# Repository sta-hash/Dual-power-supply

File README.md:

# Dual-power-supply
this provide positive and negative supply in circuit.

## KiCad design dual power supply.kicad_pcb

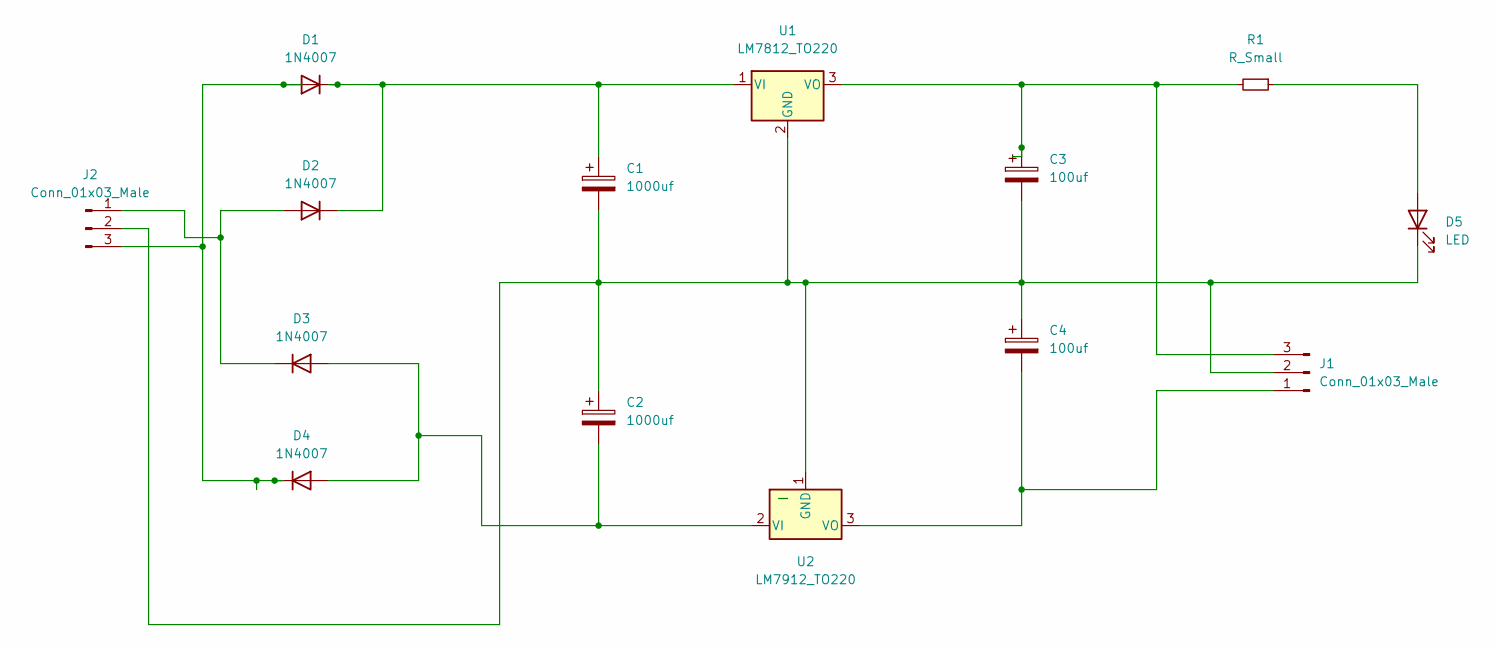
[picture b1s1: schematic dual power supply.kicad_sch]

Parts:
C1, C2: 1000uf; CP_Radial_D4.0mm_P2.00mm
C3, C4: 100uf; CP_Radial_D4.0mm_P2.00mm
D1, D2, D3, D4: 1N4007; D_DO-41_SOD81_P10.16mm_Horizontal
D5: LED; R_Axial_DIN0204_L3.6mm_D1.6mm_P1.90mm_Vertical
J1, J2: Conn_01x03_Male; SolderWire-0.1sqmm_1x03_P3.6mm_D0.4mm_OD1mm
R1: R_Small; R_Axial_DIN0204_L3.6mm_D1.6mm_P1.90mm_Vertical
U1: LM7812_TO220; TO-220-3_Vertical
U2: LM7912_TO220; TO-220-3_Vertical

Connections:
unnamed: C1.1, D1.1 (K), D2.1 (K), U1.1 (VI)
unnamed: C1.2, C2.1, C3.2, C4.1, D5.1 (K), J1.2, J2.2, U1.2 (GND), U2.1 (GND)
unnamed: C2.2, D3.2 (A), D4.2 (A), U2.2 (VI)
unnamed: C3.1, J1.3, R1.2, U1.3 (VO)
unnamed: C4.2, J1.1, U2.3 (VO)
unnamed: D1.2 (A), D4.1 (K), J2.3
unnamed: D2.2 (A), D3.1 (K), J2.1
unnamed: D5.2 (A), R1.1

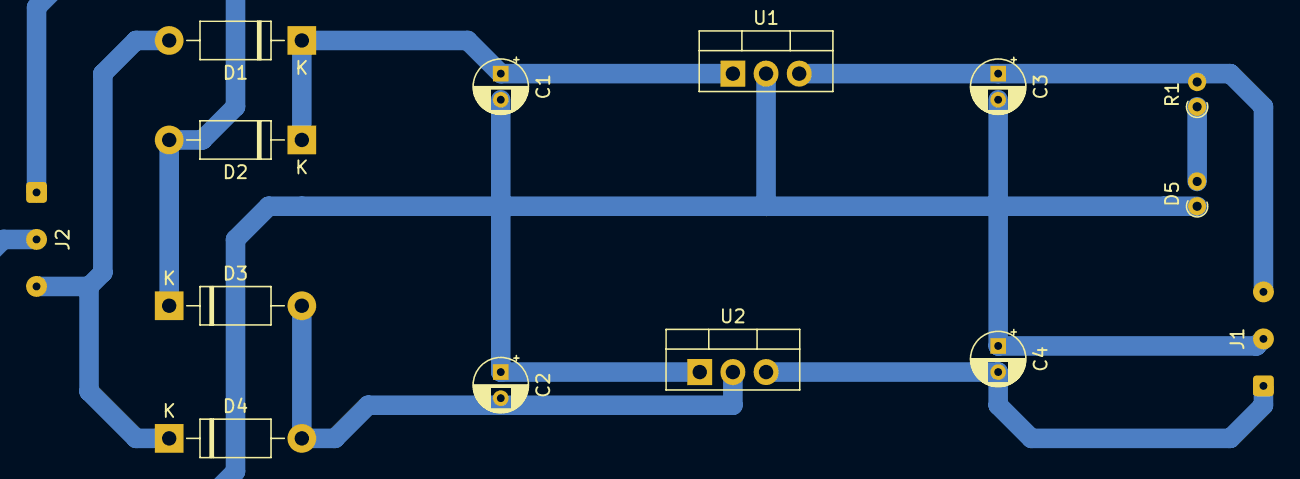
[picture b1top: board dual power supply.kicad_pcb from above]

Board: 2 copper layers, 14 parts (0 on the bottom side), 8 nets.
